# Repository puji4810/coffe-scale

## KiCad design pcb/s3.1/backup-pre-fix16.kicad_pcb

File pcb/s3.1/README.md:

# s3.1 — 双用途控制板 (rev s3.1)

一块 ESP32-S3 + NAU7802 主控板，同时服务两个产品形态：

1. **独立咖啡秤**——沿用 scale-adc-s3 的全部功能：称重前端、SPI LCD、
   双按键、蜂鸣器、USB-C 供电 / 单节锂电充放电、温度与倾斜传感。
2. **自动手冲机控制器**——同一块板通过 J10 扩展口驱动独立的
   电源/电机板（水泵、加热、流量/温度传感、喷嘴运动）。高压与功率
   驱动电路留在功率板上，本板只做控制。

> 本目录是 `pcb/scale-adc-s3/` 的改版。与 rev C 的差异：
> 90×55 规矩板框、MCU 居中、四角 M2 安装孔；新增 J10 2×10 南缘扩展口
> 与 J11 1×4 称重通道 2（VIN2）接口；NAU7802 VIN2 不再接地；
> 原 J9 扩展尝试在本版落地为 J10；测试点列移至板南侧。

## 目标

- 130×30×22 mm 单点称重传感器（ZEMIC L6D-C3-3kg 或兼容），量程 2–3 kg
- 稳定显示 0.1 g；探索 0.01 g 显示/低量程模式
- TMP102 测传感器附近温度做漂移分析；LIS2DW12 做水平/振动/敲击检测
- **第二称重通道**：NAU7802 ch2 (VIN2) 经 J11 外接第二传感器/PT1000，
  咖啡秤形态可不贴，机器形态接流量或第二称重
- **J10 扩展口**：8× GPIO（100R 串阻）+ 2× 直连 GPIO + 电源/总线排，
  对接机器电源/驱动板；R32 10k 下拉保证 XIO15（HEATER_EN 语义）
  默认安全态——裸板/未插扩展时加热线永不会被置位

## 系统结构

```
USB-C J5 ──► U8 ESD ──► R19/R20 22R ──► U4 IO19/IO20 (native USB-Serial/JTAG)
   │VBUS
   ├─► U5 TP4057 充电 ──► J6 1S Li-ion
   └─► D1/Q1 负载切换 ──► VSYS ──► U6 XC6220 3V3 1A ──► VCC_3V3 ──► U4/外设
                                  └──► U7 HT7533 ──► VDD_ADC ──► U1/U3 (安静电源轨)

L6D 3kg ──J2──► R1/R2 1k + C5/C10/C11 EMI 滤波 ──► U1 NAU7802 ch1 (I2C 0x2A)
J11 ch2 ──► C27 100n 差模电容 ──► U1 VIN2 (不再接地)
U2 LIS2DW12 (0x18)   U3 TMP102 (0x48)   共享 I2C: SDA=IO10, SCL=IO11
J7 SPI LCD          J8 按键 (TARE/MODE)          BZ1 蜂鸣器 (Q2 2N7002 驱动)
J10 2×10 ──► 机器电源/驱动板（泵/加热/流量/喷嘴）
```

## 接口

- **J2 → 称重传感器 ch1**：1=E+ (AVDD 激励), 2=E- (GND), 3=S-, 4=S+, 5=SHLD(GND)
- **J5 → USB-C**：USB 2.0，VBUS 充电/供电
- **J6 → 电池**：1=BAT+, 2=GND（JST PH 2.0）
- **J7 → LCD**：1=GND, 2=3V3, 3=SCK, 4=MOSI, 5=CS, 6=DC, 7=RST(局部 RC 上电复位), 8=BL
- **J8 → 按键/触摸**：1=GND, 2=TARE, 3=MODE, 4=3V3（4P JST PH；供 TTP223 触摸模块，老 3P 按键线仍兼容）
- **J11 → 称重通道 2 / VIN2**：1=E+, 2=E-, 3=S2-, 4=S2+；
  rev C 把 VIN2 接地作废，本版经 C27 100n 差模电容后直连 NAU7802 ch2，
  可接第二称重传感器或 PT1000（比率测量）
- **J10 → 机器电源/驱动板**（2×10 PTH，南缘居中）：

  | pin | 信号 | pin | 信号 |
  |---|---|---|---|
  | 1 | XIO38 (经 R24 100R) | 11 | EXP_5V |
  | 2 | XIO39 (R25) | 12 | 3V3 |
  | 3 | XIO40 (R26) | 13–15 | GND |
  | 4 | XIO41 (R27) | 16 | SDA |
  | 5 | XIO42 (R28) | 17 | SCL |
  | 6 | XIO14 (R29) | 18 | TXD (UART0) |
  | 7 | XIO15 (R30, R32 10k 下拉) | 19 | RXD (UART0) |
  | 8 | XIO17 (R31) | 20 | EN |
  | 9 | XIO1 (直连) | | |
  | 10 | XIO47 (直连) | | |

  A 排（1–10）= GPIO，其中 pin1–8 各经 100R 串阻限流/保护；
  B 排（11–20）= 电源 + 总线。pin20 EN 可让功率板复位主控；
  pin18/19 是 UART0，兼作烧录/调试兜底。

- **D3 (DNP) → EXP_5V→VBUS 注入**：功率板 5V 反灌选项。贴 B5819W
  = 二极管 OR（防 USB 反灌，~0.3 V 压降仍可经 TP4057 充电）；
  或 0R/飞线直通。纯秤 BOM 永不贴。

## U4 (ESP32-S3-WROOM-1-N16R8) 引脚映射

| 信号 | GPIO | 备注 |
|---|---|---|
| LCD_SCK/MOSI/CS/DC | IO4/IO5/IO6/IO7 | SPI |
| CHRG_STAT | IO8 | TP4057 开漏充电指示 |
| VBAT_SENSE | IO9 | R13/R14 100k 分压 |
| SDA / SCL | IO10 / IO11 | I2C 总线，并上 J10.16/17 |
| DRDY | IO12 | NAU7802 数据就绪 |
| INT1 | IO13 | LIS2DW12 中断（唤醒/敲击/就绪） |
| EXP_IO14 / EXP_IO15 | IO14 / IO15 | J10 pin6/pin7（经 R29/R30）；IO15 原 LCD_RST 改局部 RC POR 后释放 |
| LCD_BL | IO16 | |
| EXP_IO17 | IO17 | J10 pin8（经 R31） |
| BTN_MODE | IO18 | |
| USB D-/D+ | IO19 / IO20 | 原生 USB，经 R19/R20 22R + U8 ESD |
| BUZZ | IO21 | Q2 低侧开关 + D2 续流 |
| EXP_IO38–42 | IO38–IO42 | J10 pin1–5（经 R24–R28） |
| EXP_IO47 | IO47 | J10 pin10 直连 |
| EXP_IO1 | IO1 | J10 pin9 直连（原 UART1 候选脚，strapping 无关） |
| BTN_TARE | IO48 | 非 strapping 脚（rev C.1 从 IO46 改来） |
| UART0 TXD/RXD | TXD0 / RXD0 | TP5/TP6 + J10.18/19 |
| BOOT | IO0 | R6 10k 上拉；TP4 短接 GND = 下载模式 |
| EN | EN | R5 10k + C14 1u RC；TP3 复位 + J10.20 |
| NC | IO2/IO3, IO45/46 | IO35–37 被八线 PSRAM 占用；IO45/46 strapping 脚留空 |

## 关键设计决策

- **NAU7802 外部 AVDD = VDD_ADC 3.3 V**：AVDD_LDO/REFP/DVDD 与 ch1/ch2
  传感器激励 E+ 全部挂 U7 HT7533 安静轨，比率测量中激励波动抵消。
  固件必须保持 **AVDDS=0**（AVDD 引脚作电源输入，内部 LDO 关闭、
  VLDO 无效）。AVDD 上电即有 ~3.3 V，空板可直接量到（TP8）。
- **VIN2 解地 + J11**：rev C 把 NAU7802 ch2 输入接地作废；本版经
  C27 差模电容引出到 J11 1×4（E+/E-/S2-/S2+）。机器形态接第二称重
  或 PT1000；纯秤 BOM 可不贴 J11/C27，固件忽略 ch2。
- **J10 扩展口 = 唯一新增对外接口**：机器形态下功率板只做
  电源分配与功率驱动（泵/加热/电机驱动），所有控制、传感 I2C、
  UART、GPIO 都经 J10 进出。100R 串阻在排针侧限流保护 IO；
  R32 下拉确保 HEATER_EN 语义的 XIO15 默认低。
- **EXP_5V 供电选项（DNP）**：机器形态下功率板可经 D3 向 VBUS 侧
  反灌 5V，省掉 USB 供电线；纯秤不贴。
- **规矩板框 + 居中 MCU**：90×55 mm，MH1–MH4 M2 NPTH 四角安装孔
  (4,4)/(86,4)/(4,51)/(86,51)；U4 模组顶部居中（天线伸北缘外），
  模拟簇留西北，电源簇东南，J10 南缘居中——后续加东西走线都规整。
- **模拟岛**：西北角模拟 GND 经缝合过孔单点接主地，两层铺铜
  island_removal 开启；模拟 keepout 只挡 tracks 不挡 vias，
  北界 y24（只护 U1/U3/信号列簇）。
- **LCD_RST 局部 RC 上电复位**：沿用 rev C 方案（R21+C26 在 J7 旁）。
- **主 LDO 热预算**：U6 XC6220 1 A 指标仅指电流能力；Wi-Fi+背光+
  蜂鸣器全开须实测温升。机器形态下若贴 D3 走 EXP_5V，热预算重算。
- **电池**：J6 直挂 VSYS，无独立过放/过流切断——必须使用带保护板
  的 1S 电池包；机器形态可不贴电池，由 EXP_5V/USB 供电。

## BOM 变体

| 位号 | 纯秤 BOM | 机器 BOM |
|---|---|---|
| J10, R24–R32, D3 | J10+R24–R31 可贴可省（调试用）；R32 贴（安全下拉）；D3 不贴 | 全贴，D3 按供电方案选 B5819W 或 0R |
| J11, C27 | 可不贴（ch2 不用） | 贴（第二称重/PT1000） |
| J6, 电池 | 贴 | 可不贴 |
| J7/J8/BZ1/LCD | 贴 | 按需（机器形态可用板载 LCD 做状态屏，也可不贴走 J10 远程显示） |

## 文件

- `s3.1.kicad_sch` / `s3.1.kicad_pcb` — KiCad 10 工程
- `s3.1.pretty/` — 项目内自包含封装库（含 PinHeader_2x10_P2.54mm_Vertical 等新封装）
- `tools/gen_sch.py`, `tools/gen_pcb.py`, `tools/gen_cpl.py` — 生成脚本
- `tools/autoroute.py` — FreeRouting 自动布线（DSN/SES 往返 + 合并 +
  relock + DRC/rip-up 循环）
- `tools/route_check.py` — 候选走线几何校验器（候选路径落地前必过）
- `tools/net_islands.py`, `tools/region_dump.py` — 连通性/区域铜皮审计
- `s3.1-erc.txt` / `s3.1-drc.txt` — 验证报告

## 验证（kicad-cli 10.0）

```
kicad-cli sch erc --format report --output s3.1-erc.txt \
    --severity-all s3.1.kicad_sch
kicad-cli pcb drc --format report --output s3.1-drc.txt \
    --severity-all --refill-zones s3.1.kicad_pcb
```

布线流程：`gen_pcb.py` 只布模拟区与关键电源的手布走线并打 `(locked yes)`；
其余交 `autoroute.py`（FreeRouting）全局布线，手工修补一律先过
`route_check.py` 校验再落地并加锁。

当前状态见 `s3.1-drc.txt`；布线收敛过程见 git 历史与 `tools/fix_routes*.py`。

## Bring-up 顺序

1. 断电先量 3V3/GND、VBUS/GND、BAT/GND 无短路；上电后量 VBUS、VSYS、
   VCC_3V3、VDD_ADC。AVDD 由外部 VDD_ADC 供电（TP8），上电即应量到
   ~3.3 V，不再依赖固件使能 NAU7802 内部 LDO。
2. USB 插电脑：原生 USB-Serial/JTAG 应直接枚举；否则 TP4 短 GND +
   TP3 复位进下载模式，用 UART0（TP5/TP6 或 J10.18/19）兜底烧录。
3. I2C 扫描应见 0x18 / 0x2A / 0x48；J10.16/17 与板内 I2C 同总线，
   机器侧挂传感时注意总线负载与上拉。
4. 挂 ch1 传感器采 10/80 SPS 记录噪声/零点/重复性/温漂；
   贴 J11 时同样方法验证 ch2。
5. LIS2DW12 验证 INT1；TMP102 与传感器温漂对比。
6. 对比 LCD/背光/蜂鸣器/Wi-Fi 与 USB/电池/EXP_5V 供电下的称重读数。
7. 机器形态：先不接功率板验证 XIO* 逻辑电平与 HEATER_EN 默认低
   （R32 下拉），再对接功率板做泵/加热的低压联调，最后上高压。

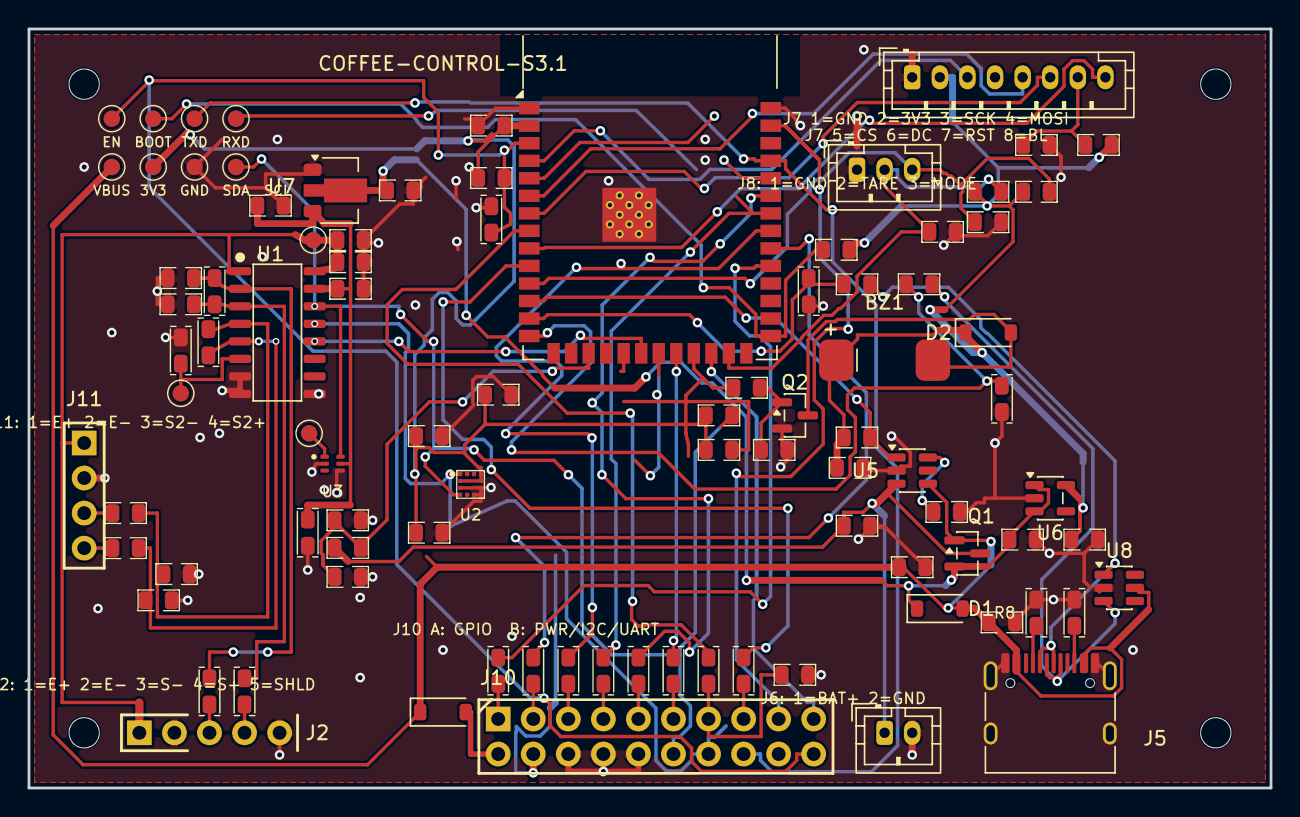
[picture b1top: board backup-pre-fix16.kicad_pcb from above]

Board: 2 copper layers, 90.0 x 55.0 mm, 96 parts (0 on the bottom side), 63 nets.

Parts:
BZ1: MLT-8530; MagneticBuzzer_CUI_CMT-8540S-SMT
C1, C2, C7, C17, C18, C19, C26: 100n; SMD_0805
C3, C25: 1u; SMD_0805
C4, C5, C27: 100n; SMD_0805_VR
C6: 100n; SMD_0805_V
C8: 4u7; SMD_0805
C9, C13, C15, C16, C20, C21, C22: 10u; SMD_0805
C10, C11: 1n; SMD_0805_F
C12: 100n; SMD_0805_F
C14: 1u; SMD_0805_V
C23, C24: DNP; SMD_0805_V
C28, C29: 1n; SMD_0805
D1, D3: B5819W; D_SOD-123
D2: 1N4148W; D_SOD-123
J2: LOADCELL; PinHeader_1x05_P2.54mm_H
J5: TYPE-C-31-M-12; USB_C_Receptacle_HRO_TYPE-C-31-M-12
J6: BAT; JST_PH_B2B-PH-K_1x02_P2.00mm_Vertical
J7: LCD; JST_PH_B8B-PH-K_1x08_P2.00mm_Vertical
J8: BTN; JST_PH_B3B-PH-K_1x03_P2.00mm_Vertical
J10: EXP; PinHeader_2x10_P2.54mm_Vertical
J11: CH2; PinHeader_1x04_P2.54mm
MH1, MH2, MH3, MH4: M2; MountingHole_M2_NPTH
Q1: AO3401A; SOT-23
Q2: 2N7002; SOT-23
R1, R2: 1k; SMD_0805_VR
R3, R4: 4k7; SMD_0805
R5, R6, R11, R15, R16, R21, R32: 10k; SMD_0805
R8, R9: 5k1; SMD_0805_VR
R10: 2k7; SMD_0805
R12, R13, R14, R18: 100k; SMD_0805
R17, R22, R23: 1k; SMD_0805
R19, R20: 22R; SMD_0805_F
R24, R25, R26, R27, R28, R29, R30, R31: 100R; SMD_0805_V
TP3: TP_EN; TestPoint_1.2mm
TP4: TP_BOOT; TestPoint_1.2mm
TP5: TP_TXD; TestPoint_1.2mm
TP6: TP_RXD; TestPoint_1.2mm
TP7: TP_VBG; TestPoint_1.2mm
TP8: TP_AVDD; TestPoint_1.2mm
TP9: TP_VBUS; TestPoint_1.2mm
TP10: TP_3V3; TestPoint_1.2mm
TP11: TP_GND; TestPoint_1.2mm
TP12: TP_SDA; TestPoint_1.2mm
TP13: TP_SCL; TestPoint_1.2mm
U1: NAU7802SGI; SOIC-16_3.9x9.9mm_P1.27mm
U2: LIS2DW12; LGA-12_2x2mm_P0.5mm_LIS2DW12
U3: TMP102; SOT-563_1.6x1.6mm_P0.5mm
U4: ESP32-S3-WROOM-1-N16R8; ESP32-S3-WROOM-1
U5: TP4057-42; SOT-23-6
U6: XC6220B331MR-G; SOT-23-5
U7: HT7533-1; SOT-89-3
U8: USBLC6-2SC6; SOT-23-6

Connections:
AVDD: C2.1, C3.1, J2.1, J11.1, TP8.1, U1.1, U1.16
BAT: C16.1, J6.1, Q1.3, R13.1, U5.3
BOOT: R6.1, TP4.1, U4.27
BTN_MODE: C19.1, J8.3, R16.2, U4.11
BTN_TARE: C18.1, J8.2, R15.2, U4.25
BUZZ: R17.1, U4.23
BUZZ_SW: BZ1.2, D2.2, Q2.3
CHRG_STAT: R11.2, U4.12, U5.1
DRDY: U1.12, U4.20
EN: C14.2, J10.20, R5.2, TP3.1, U4.3
EXP_5V: D3.2, J10.11
EXP_IO1: J10.9, U4.39
EXP_IO14: R29.1, U4.22
EXP_IO15: R30.1, U4.8
EXP_IO17: R31.1, U4.10
EXP_IO38: R24.1, U4.31
EXP_IO39: R25.1, U4.32
EXP_IO40: R26.1, U4.33
EXP_IO41: R27.1, U4.34
EXP_IO42: R28.1, U4.35
EXP_IO47: J10.10, U4.24
GND: C1.2, C2.2, C3.2, C4.2, C6.2, C7.2, C8.2, C9.2, C10.2, C11.2, C12.2, C13.2, C14.1, C15.2, C16.2, C17.2, C18.2, C19.2, C20.2, C21.2, C22.2, C23.2, C24.2, C25.2, C26.2, C28.2, C29.2, J2.2, J2.5, J5.A1, J5.A12, J5.B1, J5.B12, J5.SH, J6.2, J7.1, J8.1, J10.13, J10.14, J10.15, J11.2, Q2.2, R8.2, R9.2, R10.2, R12.2, R14.2, R18.2, R32.2, TP11.1, U1.7, U1.8, U1.9, U2.3, U2.6, U2.7, U2.8, U3.2, U3.4, U4.1, U4.40, U4.41, U5.2, U6.2, U7.1, U8.2
INT1: U2.12, U4.21
LCD_BL: J7.8, U4.9
LCD_CS: J7.5, U4.6
LCD_DC: J7.6, U4.7
LCD_MOSI: J7.4, U4.5
LCD_RST: C26.1, J7.7, R21.1
LCD_SCK: J7.3, U4.4
LC_SIG2N: J11.3, R22.1
LC_SIG2P: J11.4, R23.1
LC_SIGN: J2.3, R2.1
LC_SIGP: J2.4, R1.1
unnamed: J5.A5, R8.1
unnamed: J5.B5, R9.1
unnamed: Q2.1, R17.2, R18.1
unnamed: R10.1, U5.6
RXD: J10.19, TP6.1, U4.36
SCL: J10.17, R4.2, TP13.1, U1.13, U2.1, U3.1, U4.19
SDA: J10.16, R3.2, TP12.1, U1.14, U2.4, U3.6, U4.18
SIG2_N: C27.2, C29.1, R22.2, U1.4
SIG2_P: C27.1, C28.1, R23.2, U1.5
SIG_N: C5.2, C11.1, R2.2, U1.2
SIG_P: C5.1, C10.1, R1.2, U1.3
TXD: J10.18, TP5.1, U4.37
USB_DM: J5.A7, J5.B7, R20.1, U8.1
USB_DM_M: C24.1, R20.2, U4.13
USB_DP: J5.A6, J5.B6, R19.1, U8.3
USB_DP_M: C23.1, R19.2, U4.14
VBAT_SENSE: C17.1, R13.2, R14.1, U4.17
VBG: C4.1, TP7.1, U1.6
VBUS: C15.1, D1.2, D3.1, J5.A4, J5.A9, J5.B4, J5.B9, Q1.1, R12.1, TP9.1, U5.4, U8.5
VCC_3V3: BZ1.1, C7.1, C8.1, C9.1, C12.1, C13.1, C25.1, D2.1, J7.2, J10.12, R3.1, R4.1, R5.1, R6.2, R11.1, R15.1, R16.1, R21.2, TP10.1, U2.2, U2.9, U2.10, U4.2, U6.5
VDD_ADC: C1.1, C6.1, C20.1, U1.15, U3.5, U7.3
VSYS: C21.1, C22.1, D1.1, Q1.2, U6.1, U6.3, U7.2
XIO14: J10.6, R29.2
XIO15: J10.7, R30.2, R32.1
XIO17: J10.8, R31.2
XIO38: J10.1, R24.2
XIO39: J10.2, R25.2
XIO40: J10.3, R26.2
XIO41: J10.4, R27.2
XIO42: J10.5, R28.2

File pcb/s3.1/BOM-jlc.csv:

Reference,Qty,Value,Footprint,Description,DNP,LCSC,Note
"U1","1","NAU7802SGI","SOIC-16_3.9x9.9mm_P1.27mm","24-bit bridge-sensor ADC (Nuvoton)",,"C5180029","extended"
"U2","1","LIS2DW12","LGA-12_2x2mm_P0.5mm_LIS2DW12","3-axis accelerometer (ST) level/vibration",,"C189624","extended"
"U3","1","TMP102","SOT-563_1.6x1.6mm_P0.5mm","I2C temperature sensor (TI)",,"C99269","extended"
"U4","1","ESP32-S3-WROOM-1-N16R8","ESP32-S3-WROOM-1","Wi-Fi/BLE5 module, 16MB flash + 8MB octal PSRAM",,"C2913202","extended"
"U5","1","TP4057-42","SOT-23-6","Li-ion charger ~370mA (R10=2k7)",,"C12044",
"U6","1","XC6220B331MR-G","SOT-23-5","Main 3.3V LDO 1A high-PSRR",,"C86534","extended"
"U7","1","HT7533-1","SOT-89-3","ADC rail LDO VDD_ADC 3.3V 100mA",,"C14289",
"U8","1","USBLC6-2SC6","SOT-23-6","USB ESD protection diode array",,"C7519",
"Q1","1","AO3401A","SOT-23","P-FET load switch D=BAT S=VSYS G=VIN5V",,"C15127",
"Q2","1","2N7002","SOT-23","Buzzer low-side switch",,"C8545",
"D1","1","B5819W","D_SOD-123","VIN5V->VSYS Schottky load sharing",,"C64885",
"D2","1","1N4148W","D_SOD-123","Buzzer flyback diode",,"C81598",
"D3","1","B5819W","D_SOD-123","EXP_5V->VIN5V injection (machine build)","DNP","C64885",
"D4","1","B5819WS","D_SOD-323","USB_VBUS->VIN5V Schottky isolation, SOD-323, 1A",,"C64886",
"J5","1","TYPE-C-31-M-12","USB_C_Receptacle_HRO_TYPE-C-31-M-12","USB-C 16-pin receptacle USB 2.0",,"C165948","extended"
"BZ1","1","MLT-8530","MagneticBuzzer_CUI_CMT-8540S-SMT","Passive magnetic buzzer 8.5mm SMD",,"C94599","extended"
"R1,R2","2","1k","SMD_0805_VR","RFI/series resistor",,"C17513",
"R3,R4","2","4k7","SMD_0805","I2C SDA pull-up to VCC_3V3",,"C17673",
"R5,R6,R11,R15,R16,R21,R32","7","10k","SMD_0805","pull-up/down",,"C17414",
"R8,R9","2","5k1","SMD_0805_VR","USB-C CC1 pulldown",,"C27834",
"R10","1","2k7","SMD_0805","TP4057 PROG resistor ~370mA",,"C17530",
"R12,R13,R14,R18","4","100k","SMD_0805","Q1 gate pulldown VIN5V-GND",,"C149504",
"R17,R22,R23","3","1k","SMD_0805","RFI/series resistor",,"C17513",
"R19,R20","2","22R","SMD_0805_F","USB D+/D- series resistor",,"C17561",
"R24,R25,R26,R27,R28,R29,R30,R31","8","100R","SMD_0805_V","EXP signal series resistor (J10)",,"C17408",
"C1,C2,C7,C17,C18,C19,C26","7","100n","SMD_0805","decoupling",,"C49678",
"C3,C25","2","1u","SMD_0805","bulk decoupling",,"C28323",
"C4,C5,C27","3","100n","SMD_0805_VR","decoupling",,"C49678",
"C6","1","100n","SMD_0805_V","decoupling",,"C49678",
"C8","1","4u7","SMD_0805","LIS2DW12 VDD_IO decoupling",,"C1779",
"C9,C13,C15,C16,C20,C21,C22","7","10u","SMD_0805","rail bulk cap",,"C15850",
"C10,C11","2","1n","SMD_0805_F","common-mode filter cap to GND",,"C46653",
"C12","1","100n","SMD_0805_F","decoupling",,"C49678",
"C14","1","1u","SMD_0805_V","bulk decoupling",,"C28323",
"C23,C24","2","DNP","SMD_0805_V","USB D+/D- cap to GND (optional)","DNP","C49678",
"C28,C29","2","1n","SMD_0805","common-mode filter cap to GND",,"C46653",

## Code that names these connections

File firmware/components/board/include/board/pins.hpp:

#pragma once

/// Pin map for pcb/scale-adc-s3 rev C — the single place that binds firmware
/// to the PCB. Keep in sync with pcb/scale-adc-s3/README.md.
#include <cstdint>

namespace board::pins {

// SPI LCD (ST7789, J7). RST is a local RC power-on reset — no GPIO drives it.
inline constexpr int lcd_sck  = 4;
inline constexpr int lcd_mosi = 5;
inline constexpr int lcd_cs   = 6;
inline constexpr int lcd_dc   = 7;
inline constexpr int lcd_bl   = 16;

inline constexpr int chrg_stat  = 8;   // TP4057 open-drain charge indicator
inline constexpr int vbat_sense = 9;   // R13/R14 100k/100k divider, ADC1_CH8

// Shared I2C bus: NAU7802 (0x2A), LIS2DW12 (0x18), TMP102 (0x48)
inline constexpr int i2c_sda = 10;
inline constexpr int i2c_scl = 11;

inline constexpr int adc_drdy  = 12;   // NAU7802 conversion-ready
inline constexpr int accel_int1 = 13;  // LIS2DW12 wake/tap/drdy

inline constexpr int btn_mode = 18;
inline constexpr int btn_tare = 48;    // not a strapping pin, external pull-up

inline constexpr int usb_dm = 19;      // native USB-Serial/JTAG
inline constexpr int usb_dp = 20;

inline constexpr int buzz = 21;        // Q2 low-side switch

} // namespace board::pins

namespace board::i2c_addr {
inline constexpr std::uint8_t nau7802  = 0x2A;
inline constexpr std::uint8_t lis2dw12 = 0x18;  // SA0 = 0
inline constexpr std::uint8_t tmp102   = 0x48;
} // namespace board::i2c_addr
